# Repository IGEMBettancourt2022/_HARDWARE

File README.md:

# _HARDWARE
 This is zhere the Hardware project lives

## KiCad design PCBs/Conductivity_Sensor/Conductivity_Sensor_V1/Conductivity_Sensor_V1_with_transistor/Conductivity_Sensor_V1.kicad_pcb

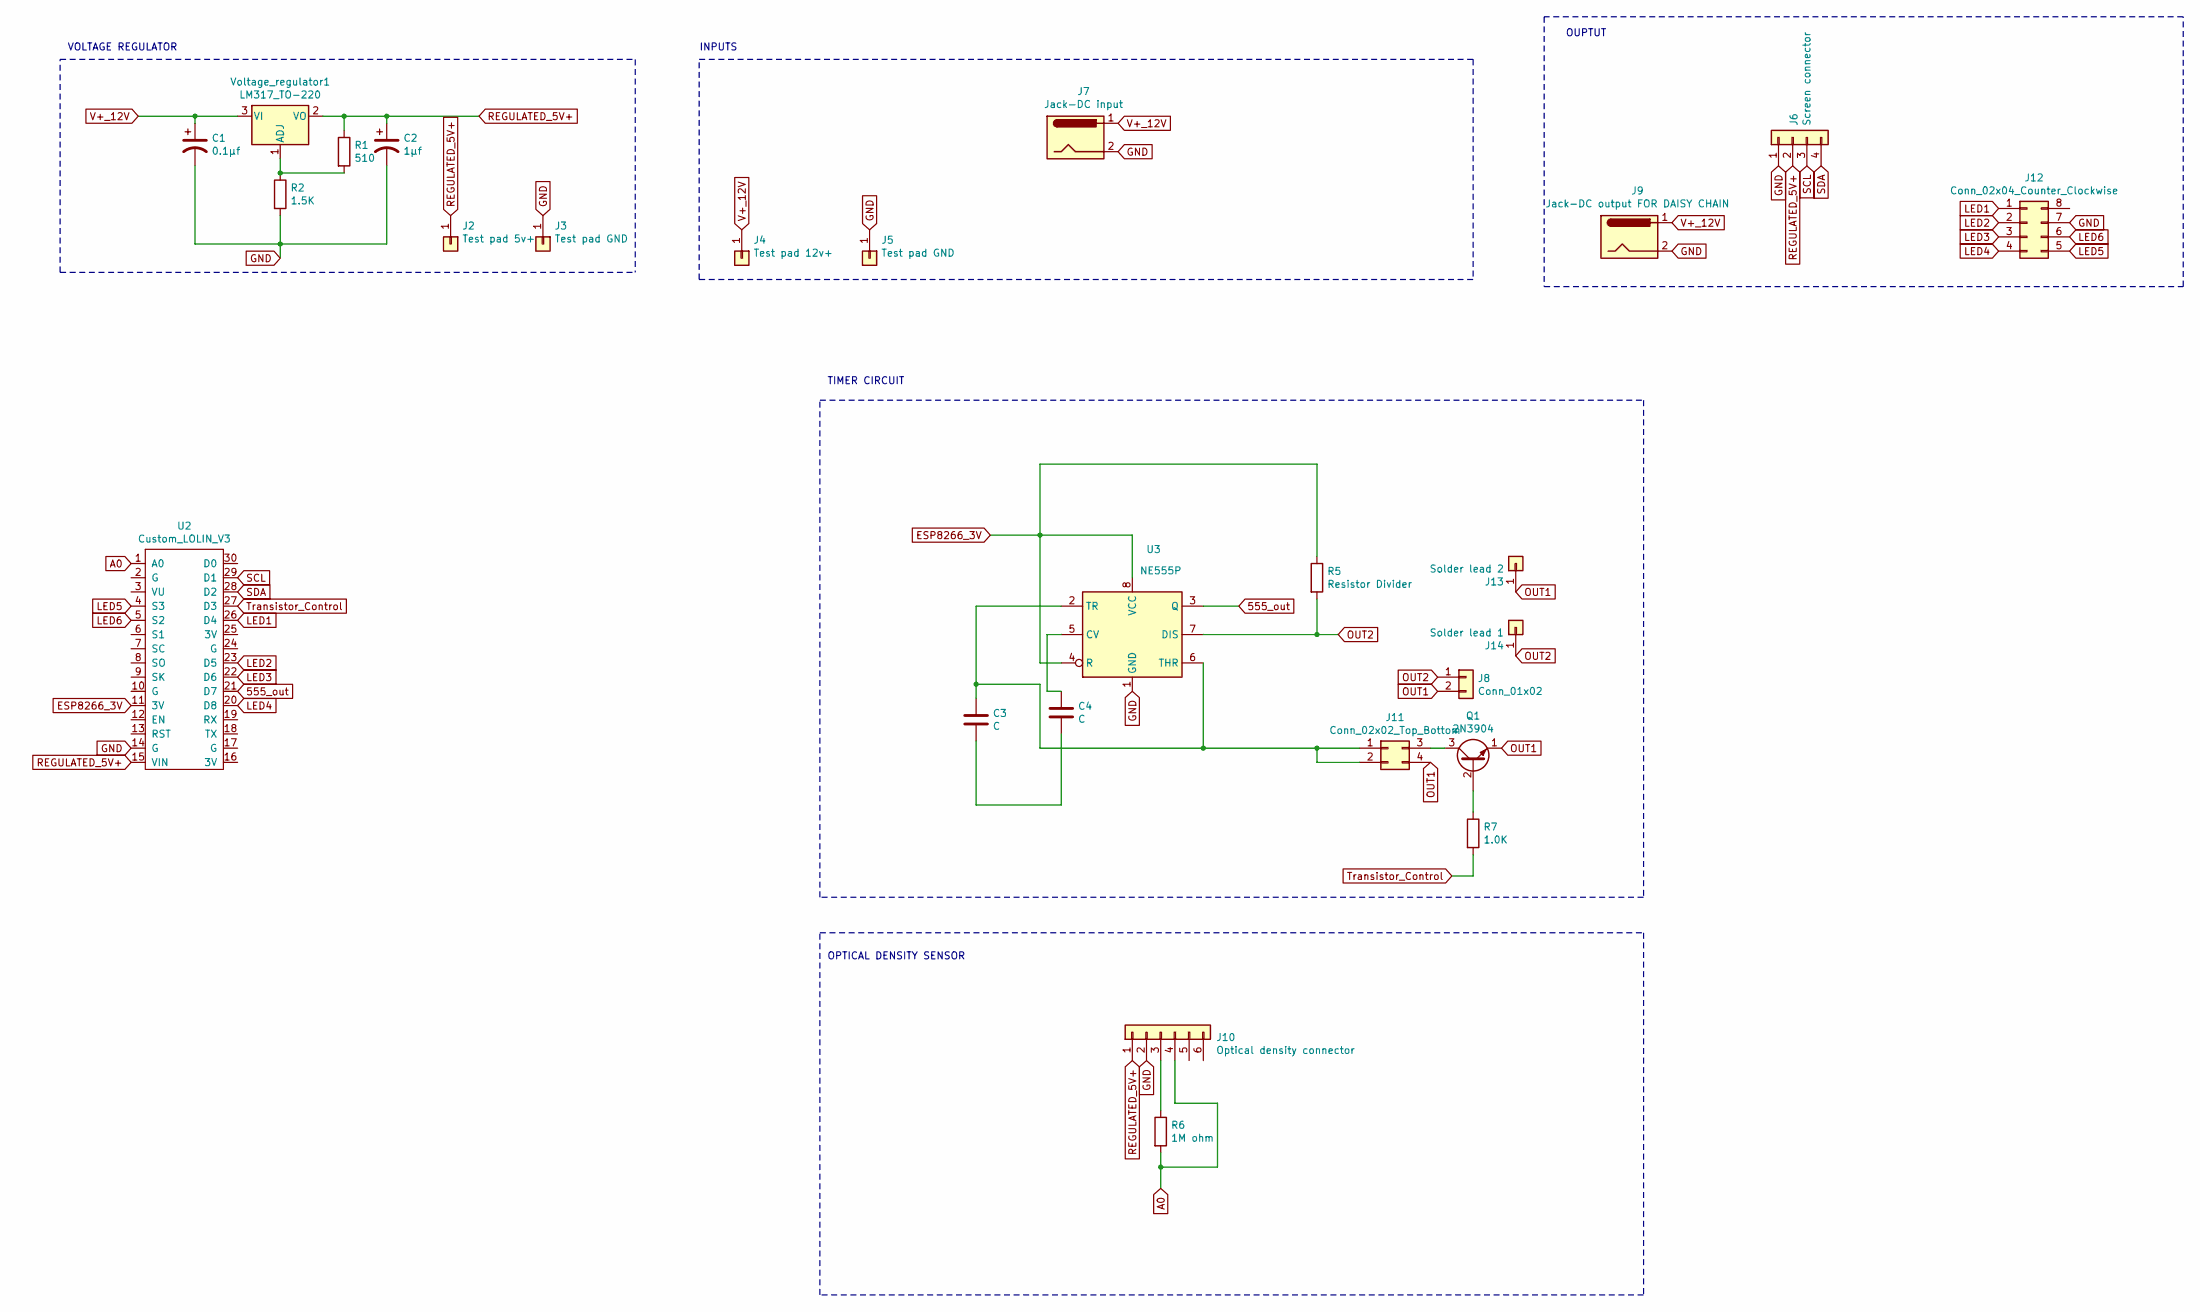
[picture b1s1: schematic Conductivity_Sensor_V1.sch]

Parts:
C1: 0.1µf; CP_Radial_D5.0mm_P2.50mm
C2: 1µf; CP_Radial_D5.0mm_P2.50mm
C3, C4: C; C_Disc_D3.4mm_W2.1mm_P2.50mm
J2: Test pad 5v+; TestPoint_Pad_4.0x4.0mm
J3, J5: Test pad GND; TestPoint_Pad_4.0x4.0mm
J4: Test pad 12v+; TestPoint_Pad_4.0x4.0mm
J6: Screen connector; PinHeader_1x04_P2.54mm_Vertical
J7: Jack-DC input; BarrelJack_CUI_PJ-063AH_Horizontal
J8: Conn_01x02; BNC_Amphenol_B6252HB-NPP3G-50_Horizontal
J9: Jack-DC output FOR DAISY CHAIN; BarrelJack_CUI_PJ-063AH_Horizontal
J10: Optical density connector; PinHeader_1x06_P2.54mm_Vertical
J11: Conn_02x02_Top_Bottom; PinHeader_2x02_P2.54mm_Vertical
J12: Conn_02x04_Counter_Clockwise; IDC-Header_2x04_P2.54mm_Horizontal
J13: Solder lead 2; TestPoint_Pad_4.0x4.0mm
J14: Solder lead 1; TestPoint_Pad_4.0x4.0mm
Q1: 2N3904; TO-92_Inline
R1: 510; R_Axial_DIN0309_L9.0mm_D3.2mm_P12.70mm_Horizontal
R2: 1.5K; R_Axial_DIN0309_L9.0mm_D3.2mm_P12.70mm_Horizontal
R5: Resistor Divider; R_Axial_DIN0309_L9.0mm_D3.2mm_P12.70mm_Horizontal
R6: 1M ohm; R_Axial_DIN0309_L9.0mm_D3.2mm_P12.70mm_Horizontal
R7: 1.0K; R_Axial_DIN0309_L9.0mm_D3.2mm_P12.70mm_Horizontal
U2: Custom_LOLIN_V3; NodeMCU-LoLinV3
U3: NE555P; DIP-8_W7.62mm
Voltage_regulator1: LM317_TO-220; TO-220-3_Vertical

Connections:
555_out: U2.21 (D7), U3.3 (Q)
A0: J10.4, R6.2, U2.1 (A0)
ESP8266_3V: R5.1, U2.11 (3V), U3.4 (R), U3.8 (VCC)
GND: C1.2, C2.2, J3.1, J5.1, J6.1, J7.2, J9.2, J10.2, J12.7, R2.2, U2.14 (G), U3.1 (GND)
LED1: J12.1, U2.26 (D4)
LED2: J12.2, U2.23 (D5)
LED3: J12.3, U2.22 (D6)
LED4: J12.4, U2.20 (D8)
LED5: J12.5, U2.4 (S3)
LED6: J12.6, U2.5 (S2)
unnamed: C3.1, J11.1, J11.2, U3.2 (TR), U3.6 (THR)
unnamed: C3.2, C4.2
unnamed: C4.1, U3.5 (CV)
unnamed: J10.3, R6.1
unnamed: J11.3, Q1.3 (C)
unnamed: Q1.2 (B), R7.1
unnamed: R1.2, R2.1, Voltage_regulator1.1 (ADJ)
OUT1: J8.2, J11.4, J13.1, Q1.1 (E)
OUT2: J8.1, J14.1, R5.2, U3.7 (DIS)
REGULATED_5V+: C2.1, J2.1, J6.2, J10.1, R1.1, U2.15 (VIN), Voltage_regulator1.2 (VO)
SCL: J6.3, U2.29 (D1)
SDA: J6.4, U2.28 (D2)
Transistor_Control: R7.2, U2.27 (D3)
V+_12V: C1.1, J4.1, J7.1, J9.1, Voltage_regulator1.3 (VI)

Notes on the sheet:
VOLTAGE REGULATOR
INPUTS
TIMER CIRCUIT
OPTICAL DENSITY SENSOR
OUPTUT

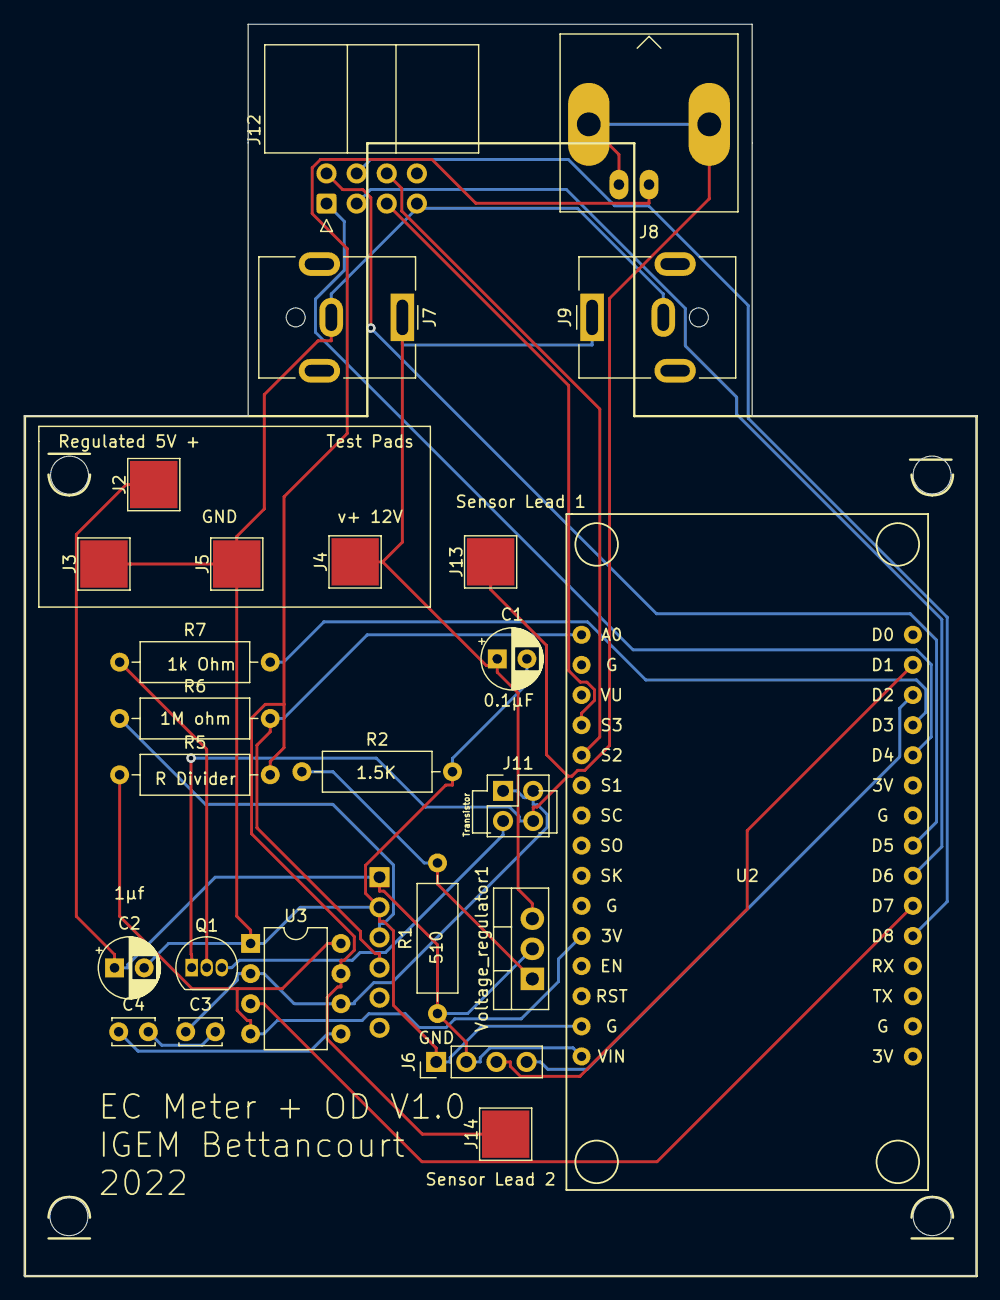
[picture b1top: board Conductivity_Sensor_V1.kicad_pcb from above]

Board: 2 copper layers, 80.3 x 105.5 mm, 26 parts (1 on the bottom side), 24 nets.

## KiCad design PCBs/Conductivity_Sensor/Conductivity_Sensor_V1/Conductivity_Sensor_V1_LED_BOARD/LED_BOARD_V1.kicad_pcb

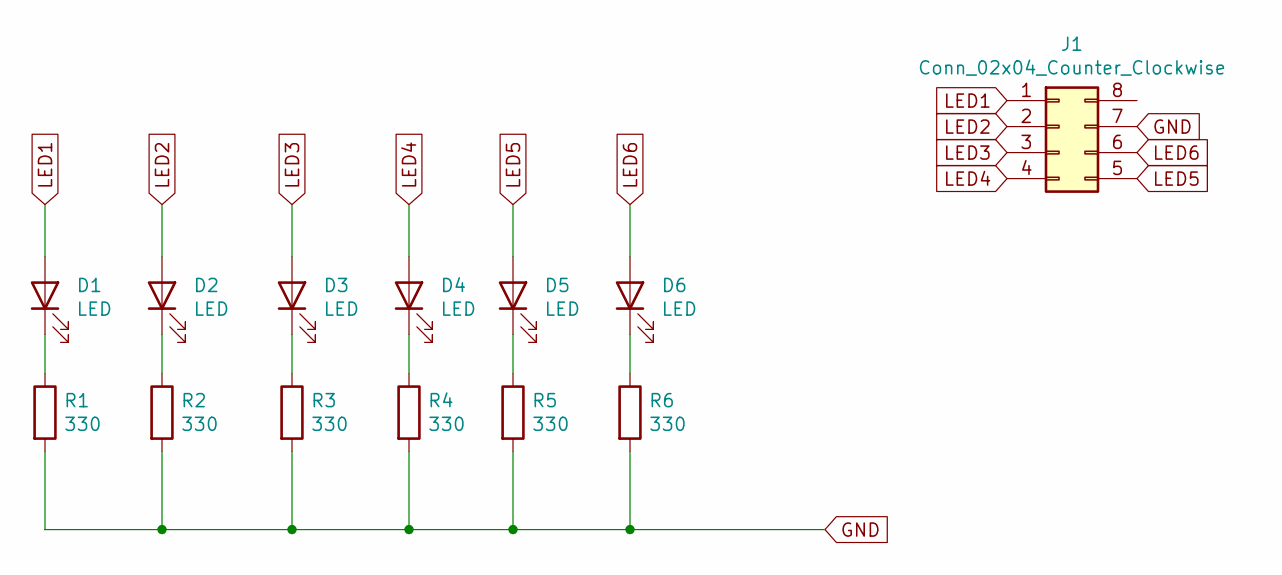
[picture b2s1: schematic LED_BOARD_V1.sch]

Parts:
D1, D2, D3, D4, D5, D6: LED; LED_D5.0mm_IRGrey
J1: Conn_02x04_Counter_Clockwise; IDC-Header_2x04_P2.54mm_Horizontal
R1, R2, R3, R4, R5, R6: 330; R_Axial_DIN0309_L9.0mm_D3.2mm_P12.70mm_Horizontal

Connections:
GND: J1.7, R1.2, R2.2, R3.2, R4.2, R5.2, R6.2
LED1: D1.2 (A), J1.1
LED2: D2.2 (A), J1.2
LED3: D3.2 (A), J1.3
LED4: D4.2 (A), J1.4
LED5: D5.2 (A), J1.5
LED6: D6.2 (A), J1.6
unnamed: D1.1 (K), R1.1
unnamed: D2.1 (K), R2.1
unnamed: D3.1 (K), R3.1
unnamed: D4.1 (K), R4.1
unnamed: D5.1 (K), R5.1
unnamed: D6.1 (K), R6.1

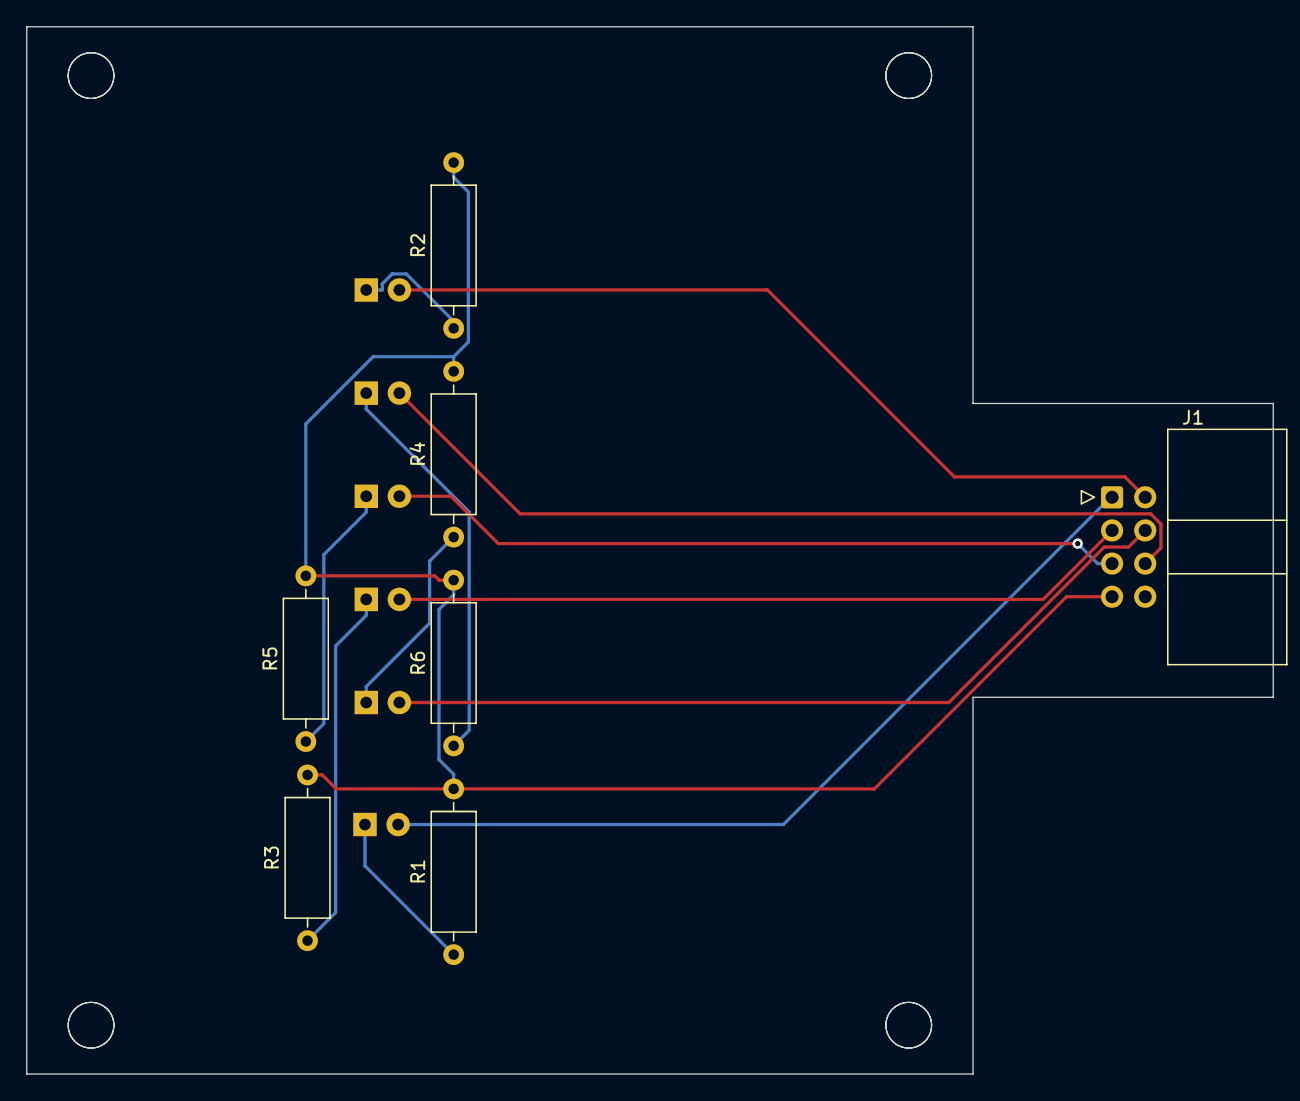
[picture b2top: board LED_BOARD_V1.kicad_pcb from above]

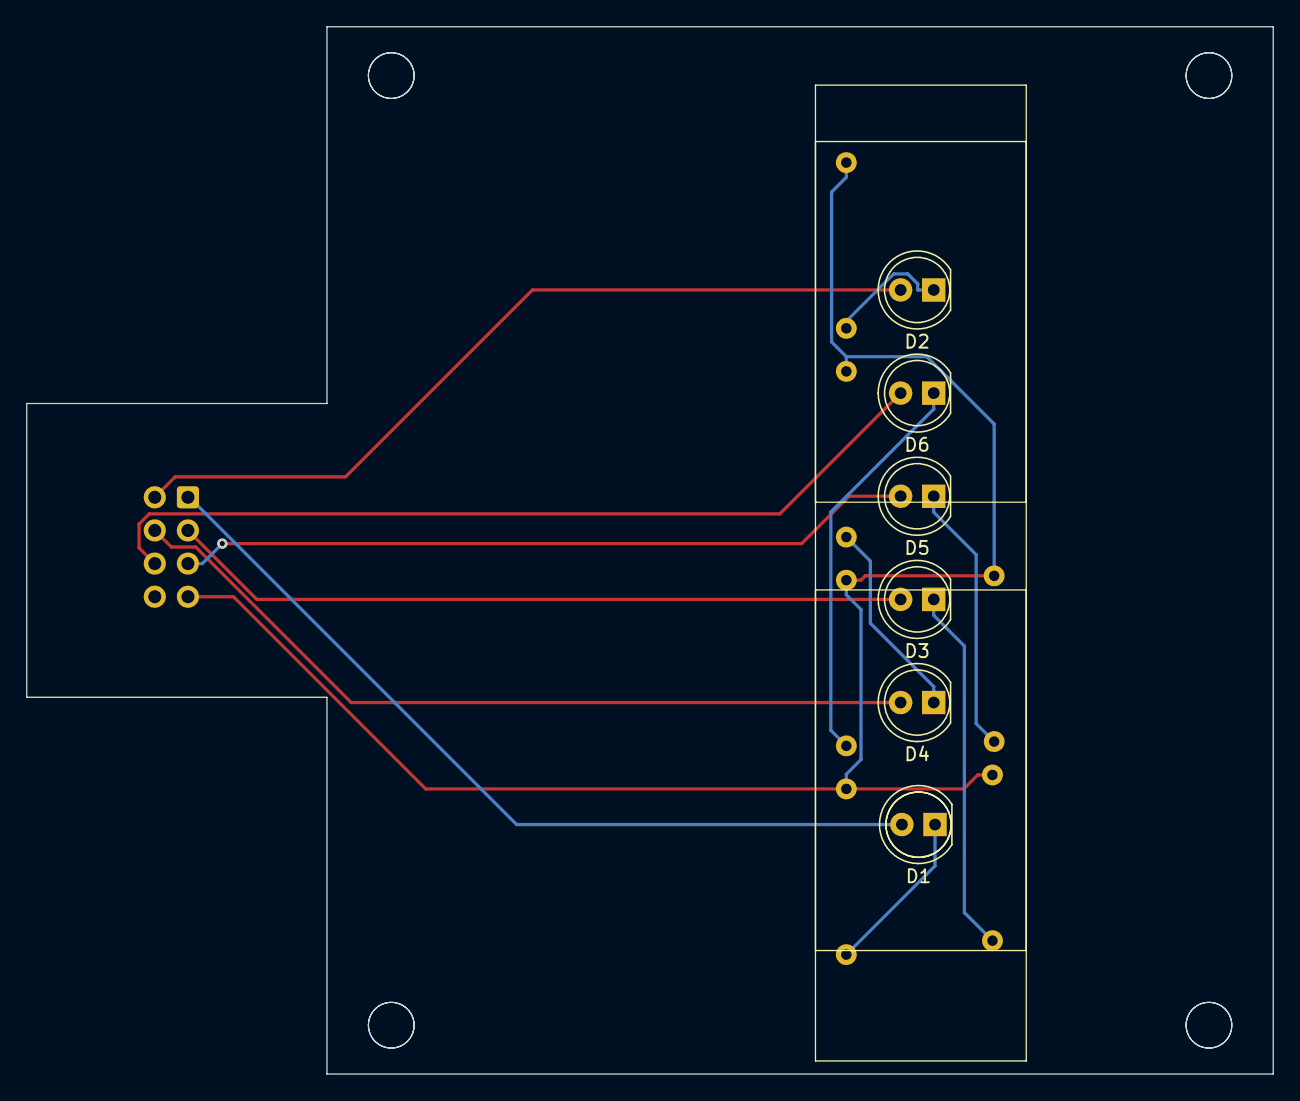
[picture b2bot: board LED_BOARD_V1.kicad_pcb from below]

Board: 2 copper layers, 95.5 x 80.3 mm, 13 parts (6 on the bottom side), 13 nets.

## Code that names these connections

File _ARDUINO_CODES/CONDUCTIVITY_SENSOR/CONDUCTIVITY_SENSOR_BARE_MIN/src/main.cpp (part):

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int delay_between_sanples = 500;
int delay_between_round = 1000;

// int LED1 = 16;
int LED2 = 14;
int LED3 = 12;
int LED4 = 15;
int LED5 = 10;
// int LED6 = 9;

// Declaration for an SSD1306 display connected to I2C (SDA, SCL pins)
#define OLED_RESET -1 // Reset pin # (or -1 if sharing Arduino reset pin)
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  display.clearDisplay();

  pinMode(ledPin, OUTPUT);
  // pinMode(LED1, OUTPUT);
  pinMode(LED2, OUTPUT);
  pinMode(LED3, OUTPUT);
  pinMode(LED4, OUTPUT);
  pinMode(LED5, OUTPUT);
  // pinMode(LED6, OUTPUT);

  digitalWrite(ledPin, LOW);
  // digitalWrite(LED1, LOW);
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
